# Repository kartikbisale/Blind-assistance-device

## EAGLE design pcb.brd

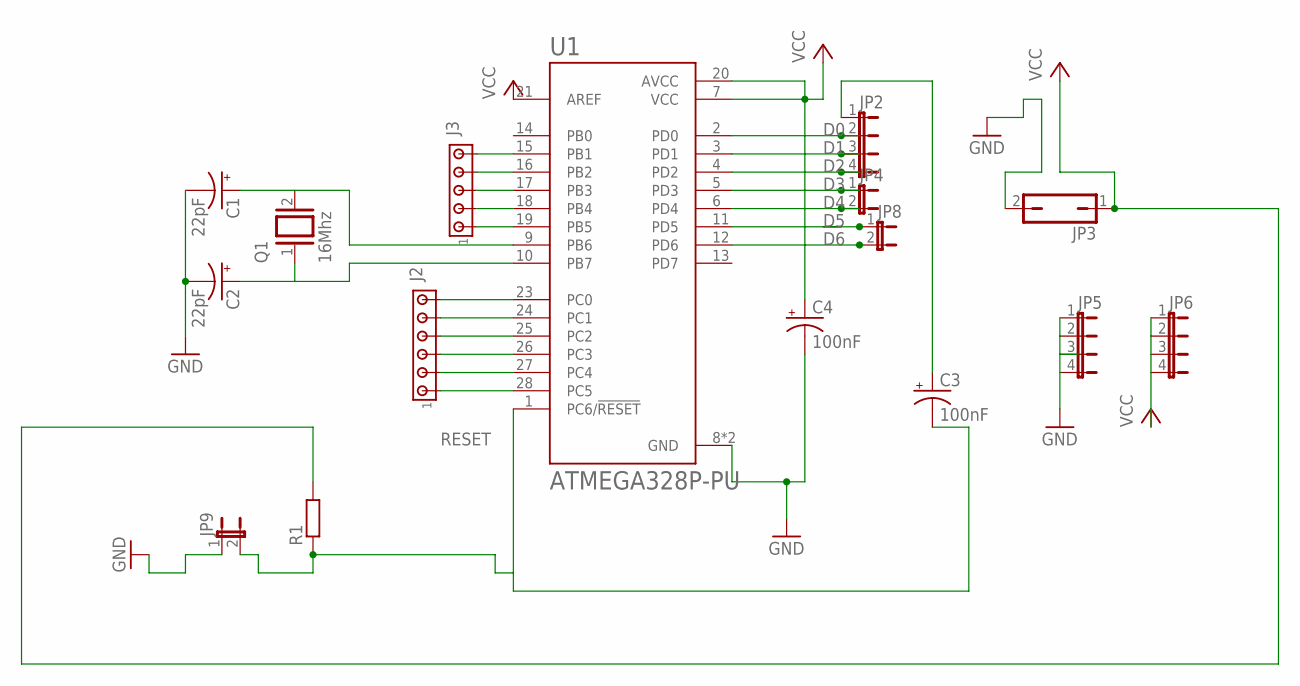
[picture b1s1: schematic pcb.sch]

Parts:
C1, C2: 22pF; E2,5-5
C3, C4: 100nF; E2,5-5
J2: MTA06-100; 10X06MTA
J3: MTA05-100; 10X05MTA
JP2, JP5, JP6: JP4E; JP4
JP3: JP1Q; JP1
JP4, JP8, JP9: JP1E; JP1
Q1: 16Mhz; QS
R1: R-EU_0204/5; 0204/5
U1: ATMEGA328P-PU; DIP794W46P254L2967H457Q28B

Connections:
D0: JP2.2, U1.2 (PD0)
D1: JP2.3, U1.3 (PD1)
D2: JP2.4, U1.4 (PD2)
D3: JP4.1, U1.5 (PD3)
D4: JP4.2, U1.6 (PD4)
D5: JP8.1, U1.11 (PD5)
D6: JP8.2, U1.12 (PD6)
GND: C1.-, C2.-, C4.-, JP3.2, JP5.1, JP5.2, JP5.3, JP5.4, JP9.1, U1.8 (GND), U1.22 (GND)
unnamed: J2.6, U1.23 (PC0)
unnamed: C3.+, JP2.1
unnamed: J2.5, U1.24 (PC1)
unnamed: J2.4, U1.25 (PC2)
unnamed: J2.3, U1.26 (PC3)
unnamed: J2.2, U1.27 (PC4)
unnamed: J2.1, U1.28 (PC5)
unnamed: J3.5, U1.15 (PB1)
unnamed: J3.4, U1.16 (PB2)
unnamed: J3.3, U1.17 (PB3)
unnamed: J3.2, U1.18 (PB4)
unnamed: J3.1, U1.19 (PB5)
unnamed: C1.+, Q1.2, U1.9 (PB6)
unnamed: C2.+, Q1.1, U1.10 (PB7)
RESET: C3.-, JP9.2, R1.1, U1.1 (PC6/!RESET)
VCC: C4.+, JP3.1, JP6.1, JP6.2, JP6.3, JP6.4, R1.2, U1.7 (VCC), U1.20 (AVCC), U1.21 (AREF)

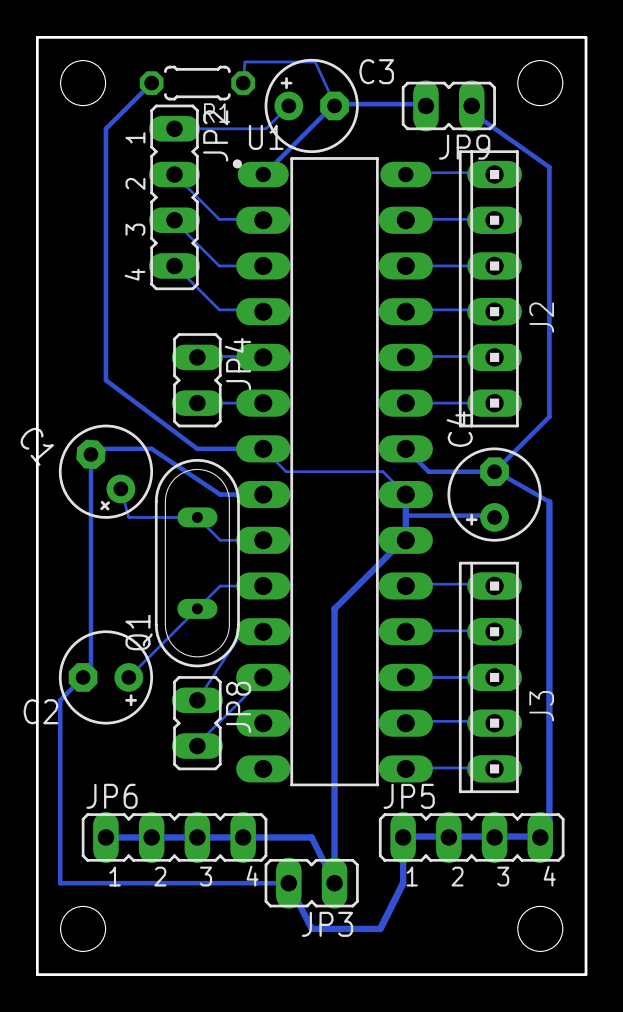
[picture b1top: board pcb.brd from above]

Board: 2 copper layers, 30.5 x 52.1 mm, 16 parts (0 on the bottom side), 24 nets.
